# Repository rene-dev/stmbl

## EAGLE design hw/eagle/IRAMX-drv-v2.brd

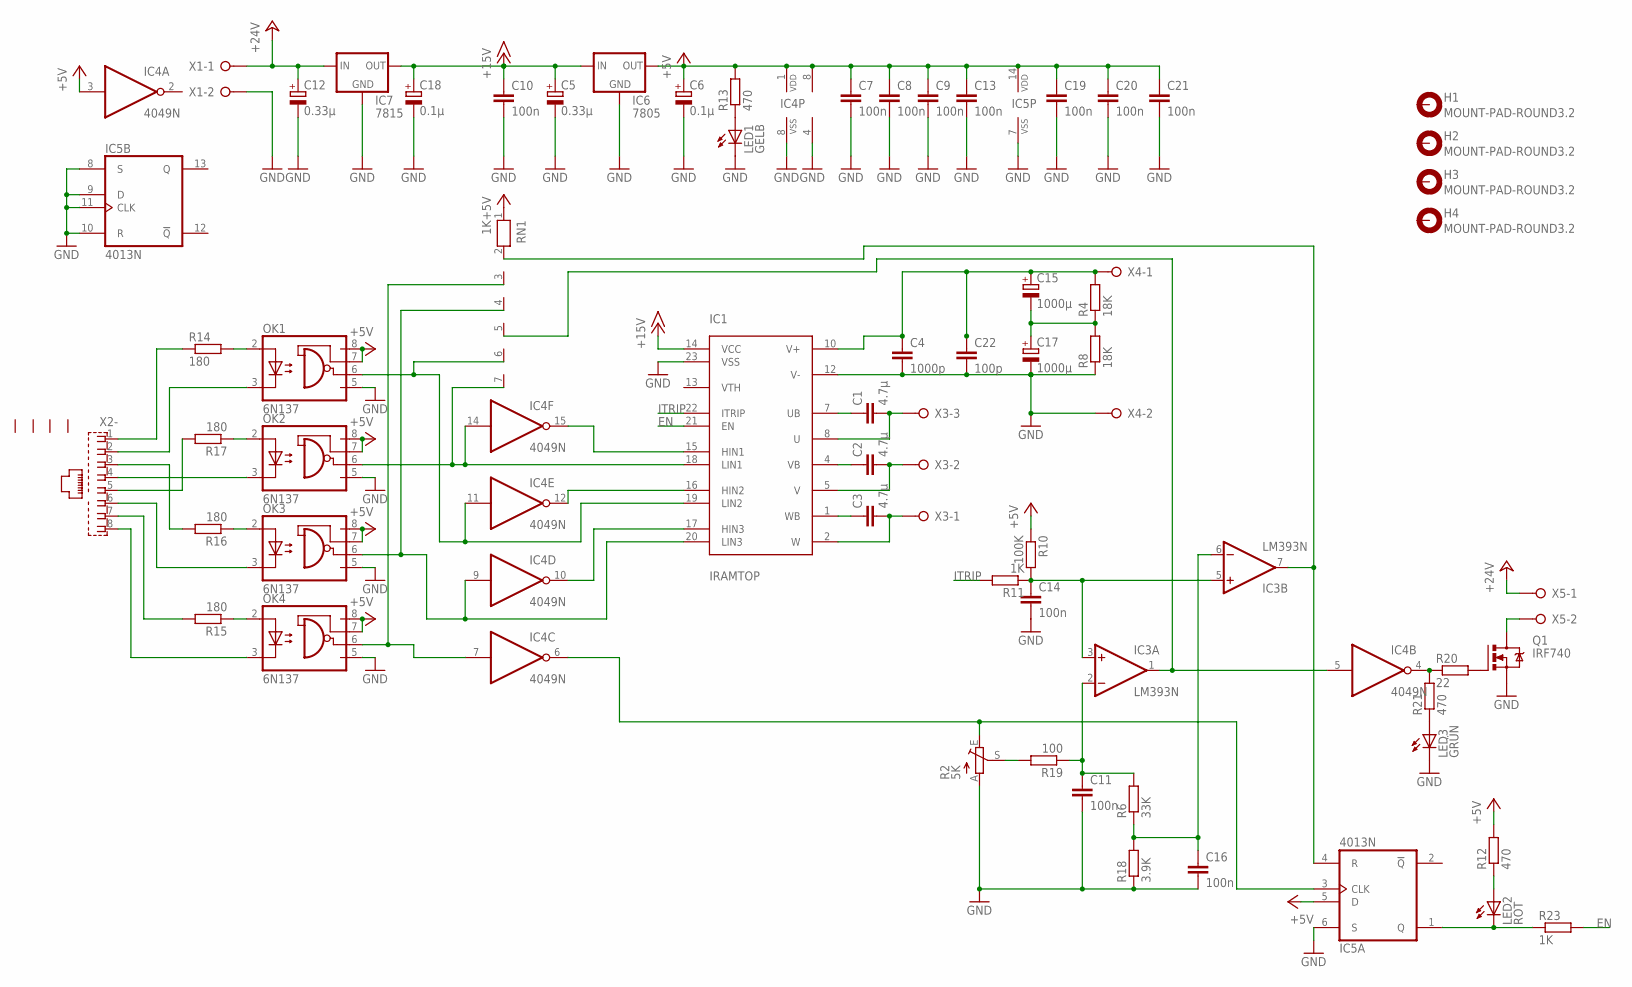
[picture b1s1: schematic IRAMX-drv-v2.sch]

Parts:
C1, C2, C3: 4.7µ; C5B7.2
C4: 1000p; C5B5
C5, C12: 0.33µ; E2,5-5
C6, C18: 0.1µ; E2,5-5
C7, C8, C9, C10, C11, C13, C14, C16, C19, C20, C21: 100n; C050-025X075
C15, C17: 1000µ; EB25D
C22: 100p; C150-054X183
H1, H2, H3, H4: MOUNT-PAD-ROUND3.2; 3,2-PAD
IC1: IRAMTOP; SIP23_TOP
IC3: LM393N; DIL08
IC4: 4049N; DIL16
IC5: 4013N; DIL14
IC6: 7805; 78XXS
IC7: 7815; 78XXS
LED1: GELB; LED5MM
LED2: ROT; LED5MM
LED3: GRÜN; LED5MM
OK1, OK2, OK3, OK4: 6N137; DIL08
Q1: IRF740; TO220BV
R2: 5K; CA6V
R4, R8: 18K; CER
R6: 33K; 0204/7
R10: 100K; 0204/7
R11, R23: 1K; 0204/7
R12, R13, R21: 470; 0204/7
R14, R15, R16, R17: 180; 0204V
R18: 3.9K; 0204/7
R19: 100; 0204/7
R20: 22; 0204/7
RN1: 1K; RN-7
X1, X4, X5: W237-02P; W237-132
X2: RJ45
X3: W237-03P; W237-133

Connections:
+5V: C6.+, C7.1, C8.1, C9.1, C13.1, C19.1, C20.1, C21.1, IC3.8 (V+), IC4.1 (VDD), IC4.3 (I), IC5.5 (D), IC5.14 (VDD), IC6.OUT, OK1.7 (VE), OK1.8 (VCC), OK2.7 (VE), OK2.8 (VCC), OK3.7 (VE), OK3.8 (VCC), OK4.7 (VE), OK4.8 (VCC), R10.1, R12.2, R13.2, RN1.1
+15V: C5.+, C10.1, C18.+, IC1.14 (VCC), IC6.IN, IC7.OUT
+24V: C12.+, IC7.IN, X1.1, X5.1
EN: IC1.21 (EN), R23.2
GND: C4.2, C5.-, C6.-, C7.2, C8.2, C9.2, C10.2, C11.2, C12.-, C13.2, C14.2, C16.2, C17.-, C18.-, C19.2, C20.2, C21.2, C22.2, IC1.12 (V-), IC1.23 (VSS), IC3.4 (V-), IC4.8 (VSS), IC5.6 (S), IC5.7 (VSS), IC5.8 (S), IC5.9 (D), IC5.10 (R), IC5.11 (CLK), IC6.GND, IC7.GND, LED1.K (C), LED3.K (C), OK1.5 (GND), OK2.5 (GND), OK3.5 (GND), OK4.5 (GND), Q1.S, R2.A, R8.P$1 (1), R18.1, X1.2, X4.2
ITRIP: IC1.22 (ITRIP), R11.2
unnamed: C1.1, IC1.7 (UB)
unnamed: C1.2, IC1.8 (U), X3.3
unnamed: C2.1, IC1.4 (VB)
unnamed: C2.2, IC1.5 (V), X3.2
unnamed: C3.1, IC1.1 (WB)
unnamed: C3.2, IC1.2 (W), X3.1
unnamed: LED2.A, R12.1
unnamed: C14.1, IC3.3 (+IN), IC3.5 (+IN), R10.2, R11.1
unnamed: LED3.A, R21.1
unnamed: IC3.1 (OUT), IC4.5 (I), RN1.5
unnamed: C15.-, C17.+, R4.P$1 (1), R8.P$2 (2)
unnamed: IC1.15 (HIN1), IC4.15 (O)
unnamed: IC1.16 (HIN2), IC4.12 (O)
unnamed: IC4.6 (O), IC5.3 (CLK), R2.E
unnamed: IC1.17 (HIN3), IC4.10 (O)
unnamed: OK3.3 (C), X2.6
unnamed: R16.2, X2.3
unnamed: OK4.3 (C), X2.8
unnamed: OK2.3 (C), X2.4
unnamed: OK1.3 (C), X2.2
unnamed: OK1.2 (A), R14.2
unnamed: R17.2, X2.5
unnamed: R15.2, X2.7
unnamed: IC1.18 (LIN1), IC4.14 (I), OK2.6 (VO), RN1.7
unnamed: R2.S, R19.2
unnamed: Q1.D, X5.2
unnamed: C11.1, IC3.2 (-IN), R6.2, R19.1
unnamed: IC5.1 (Q), LED2.K (C), R23.1
unnamed: IC4.7 (I), OK4.6 (VO), RN1.3
unnamed: R14.1, X2.1
unnamed: OK4.2 (A), R15.1
unnamed: OK3.2 (A), R16.1
unnamed: OK2.2 (A), R17.1
unnamed: IC1.19 (LIN2), IC4.11 (I), OK1.6 (VO), RN1.6
unnamed: C16.1, IC3.6 (-IN), R6.1, R18.2
unnamed: C4.1, C15.+, C22.1, IC1.10 (V+), R4.P$2 (2), X4.1
unnamed: IC1.20 (LIN3), IC4.9 (I), OK3.6 (VO), RN1.4
unnamed: IC4.4 (O), R20.1, R21.2
unnamed: Q1.G, R20.2
unnamed: IC3.7 (OUT), IC5.4 (R), RN1.2
unnamed: LED1.A, R13.1

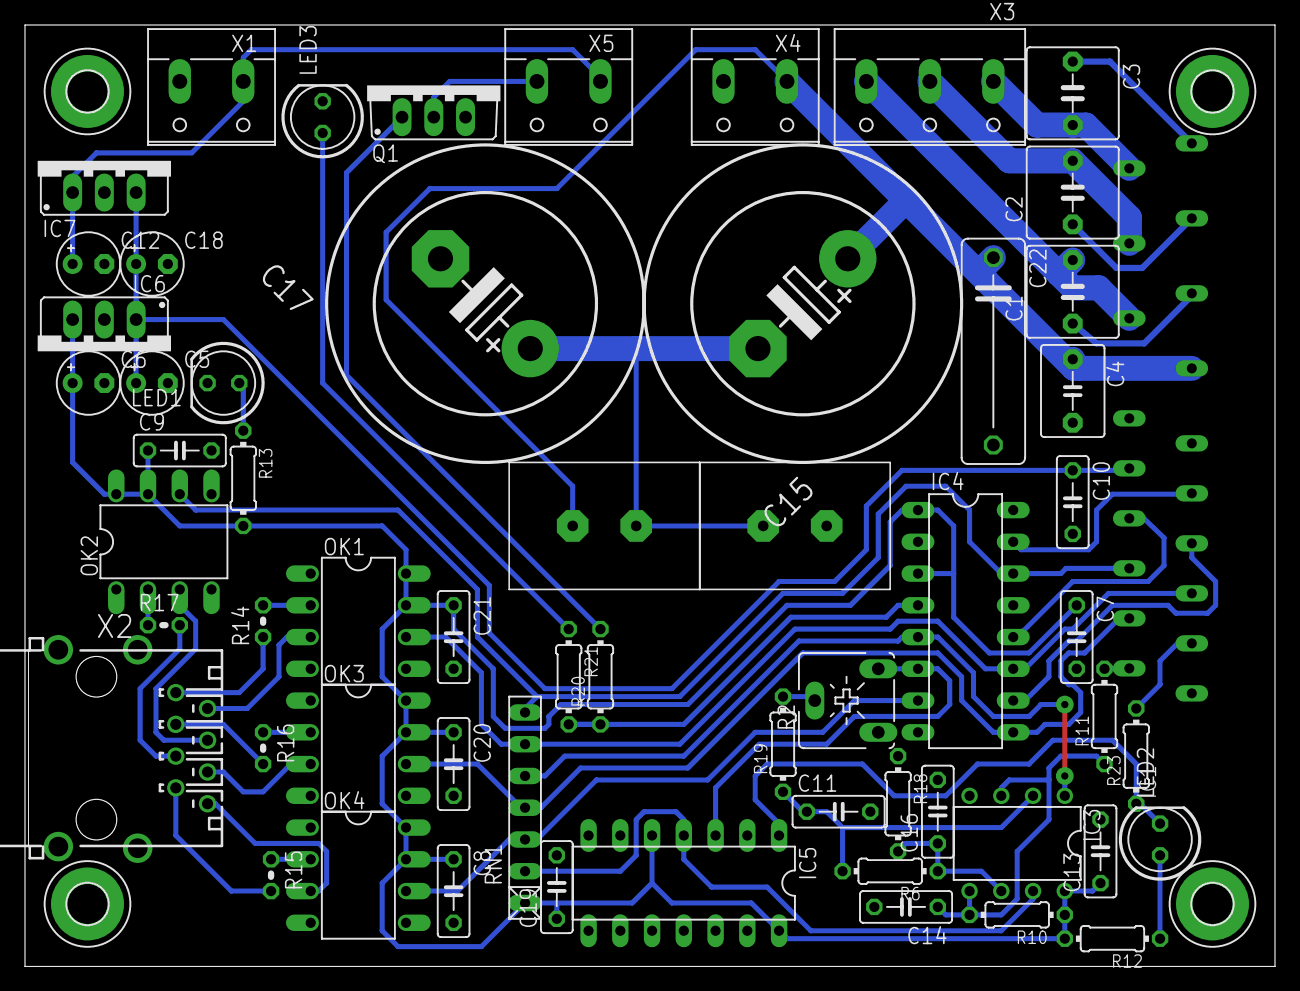
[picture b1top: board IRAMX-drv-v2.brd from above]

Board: 2 copper layers, 100.0 x 75.3 mm, 63 parts (0 on the bottom side), 47 nets.

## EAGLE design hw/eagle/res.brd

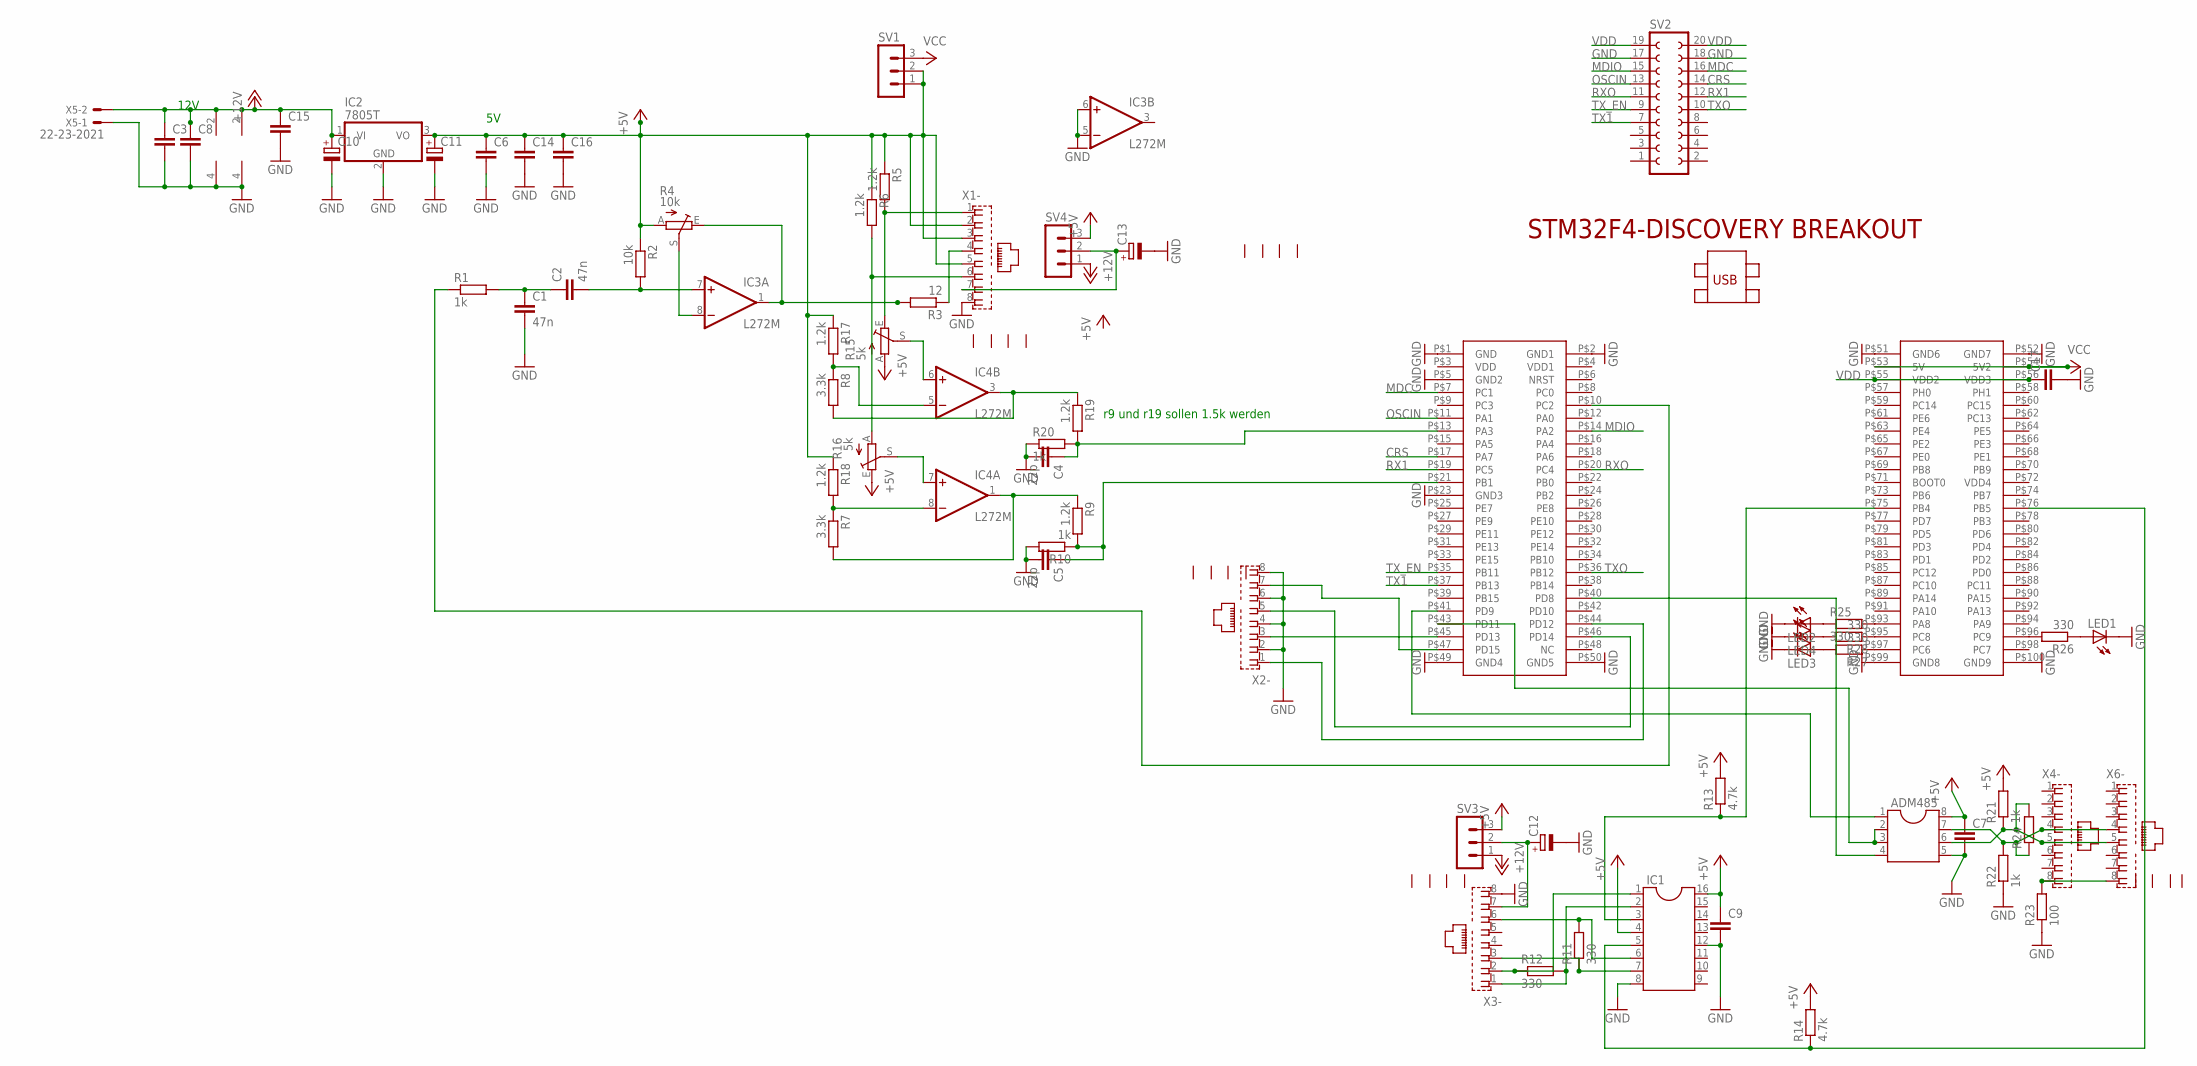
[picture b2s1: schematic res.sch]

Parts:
ADM485: DIL8; DIL08
C1, C2: 47n; C050-025X075
C3, C6, C7, C8, C9, C14, C15, C16, C17: C-EU050-025X075; C050-025X075
C4, C5: 22p; C050-025X075
C10, C11, C12, C13: CPOL-EUE2.5-5; E2,5-5
IC1: DIL16
IC2: 7805T; TO220H
IC3, IC4: L272M; DIL08
LED1, LED2, LED3, LED4: LED3MM
R1, R10, R20, R21, R22: 1k; 0204/7
R2: 10k; 0204/7
R3: 12; 0204/7
R4: 10k; CA6V
R5, R6, R9, R17, R18, R19: 1.2k; 0204/7
R7, R8: 3.3k; 0204/7
R11, R12, R25, R26, R27, R28: 330; 0204/7
R13, R14: 4.7k; 0204/7
R15, R16: 5k; CA6V
R23: 100; 0204/7
R24: R-EU_0204/7; 0204/7
SV1, SV3, SV4: MA03-1
SV2: FE10-2W
U$1: STM32F4-DISCOVERY
X1, X2, X3, X4, X6: RJ45
X5: 22-23-2021

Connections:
+5V: ADM485.8, C6.1, C7.1, C9.1, C11.+, C14.1, C16.1, IC1.4, IC1.16, IC2.3 (VO), R2.1, R4.A, R5.1, R6.1, R13.2, R14.2, R15.A, R16.E, R17.1, R18.1, R21.2, SV1.1, SV1.2, SV3.3, SV4.3, X1.2, X1.3, X1.5
+12V: C3.1, C8.1, C10.+, C15.1, IC2.1 (VI), IC3.2 (V+), IC4.2 (V+), SV3.1, SV4.1, X5.2
CRS: SV2.14, U$1.P$17 (PA7)
GND: ADM485.5, C1.2, C3.2, C4.2, C5.2, C6.2, C7.2, C8.2, C9.2, C10.-, C11.-, C12.-, C13.-, C14.2, C15.2, C16.2, C17.2, IC1.8, IC1.12, IC2.2 (GND), IC3.4 (GND), IC3.5 (-IN), IC3.6 (+IN), IC4.4 (GND), LED1.K (C), LED2.K (C), LED3.K (C), LED4.K (C), R10.2, R20.1, R22.1, R23.1, SV2.17, SV2.18, U$1.P$1 (GND), U$1.P$2 (GND1), U$1.P$5 (GND2), U$1.P$23 (GND3), U$1.P$49 (GND4), U$1.P$50 (GND5), U$1.P$51 (GND6), U$1.P$52 (GND7), U$1.P$99 (GND8), U$1.P$100 (GND9), X1.8, X2.2, X2.4, X2.6, X2.8, X3.8, X5.1
MDC: SV2.16, U$1.P$7 (PC1)
MDIO: SV2.15, U$1.P$14 (PA2)
unnamed: IC3.8 (-IN), R4.S
unnamed: IC3.1 (OUT), R3.2, R4.E
unnamed: C2.2, IC3.7 (+IN), R2.2
unnamed: R1.1, U$1.P$10 (PC2)
unnamed: C1.1, C2.1, R1.2
unnamed: R3.1, X1.4
unnamed: R6.2, R16.A, X1.6
unnamed: R5.2, R15.E, X1.1
unnamed: IC4.5 (-IN), R8.1, R17.2
unnamed: IC4.8 (-IN), R7.1, R18.2
unnamed: IC4.3 (OUT), R8.2, R19.1
unnamed: IC4.1 (OUT), R7.2, R9.1
unnamed: U$1.P$47 (PD15), X2.7
unnamed: C12.+, SV3.2, X3.7
unnamed: U$1.P$44 (PD12), X2.1
unnamed: IC1.6, R11.2, X3.6
unnamed: U$1.P$46 (PD14), X2.5
unnamed: U$1.P$45 (PD13), X2.3
unnamed: C4.1, R19.2, R20.2, U$1.P$13 (PA3)
unnamed: IC4.6 (+IN), R15.S
unnamed: IC1.3, R13.1, U$1.P$75 (PB4)
unnamed: IC1.5, R14.1, U$1.P$76 (PB5)
unnamed: IC1.2, R12.2, X3.1
unnamed: IC1.1, R12.1, X3.2
unnamed: IC1.7, R11.1, X3.3
unnamed: C13.+, SV4.2, X1.7
unnamed: IC4.7 (+IN), R16.S
unnamed: ADM485.4, U$1.P$40 (PD8)
unnamed: C5.1, R9.2, R10.1, U$1.P$21 (PB1)
unnamed: ADM485.1, U$1.P$41 (PD9)
unnamed: ADM485.2, ADM485.3, U$1.P$43 (PD11)
unnamed: ADM485.6, R21.1, R24.2, X4.5, X6.5
unnamed: ADM485.7, R22.2, R24.1, X4.4, X6.4
unnamed: R23.2, X4.8, X6.8
unnamed: LED2.A, R25.1
unnamed: R26.2, U$1.P$96 (PC9)
unnamed: R27.1, U$1.P$97 (PC6)
unnamed: R28.1, U$1.P$95 (PC8)
unnamed: LED1.A, R26.1
unnamed: R25.2, U$1.P$93 (PA8)
unnamed: LED3.A, R27.2
unnamed: LED4.A, R28.2
OSCIN: SV2.13, U$1.P$11 (PA1)
RX1: SV2.12, U$1.P$19 (PC5)
RXO: SV2.11, U$1.P$20 (PC4)
TX1: SV2.7, U$1.P$37 (PB13)
TXO: SV2.10, U$1.P$36 (PB12)
TX_EN: SV2.9, U$1.P$35 (PB11)
VCC: SV1.3, U$1.P$53 (5V), U$1.P$54 (5V2)
VDD: C17.1, SV2.19, SV2.20, U$1.P$55 (VDD2), U$1.P$56 (VDD3)

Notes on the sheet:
12V
r9 und r19 sollen 1.5k werden

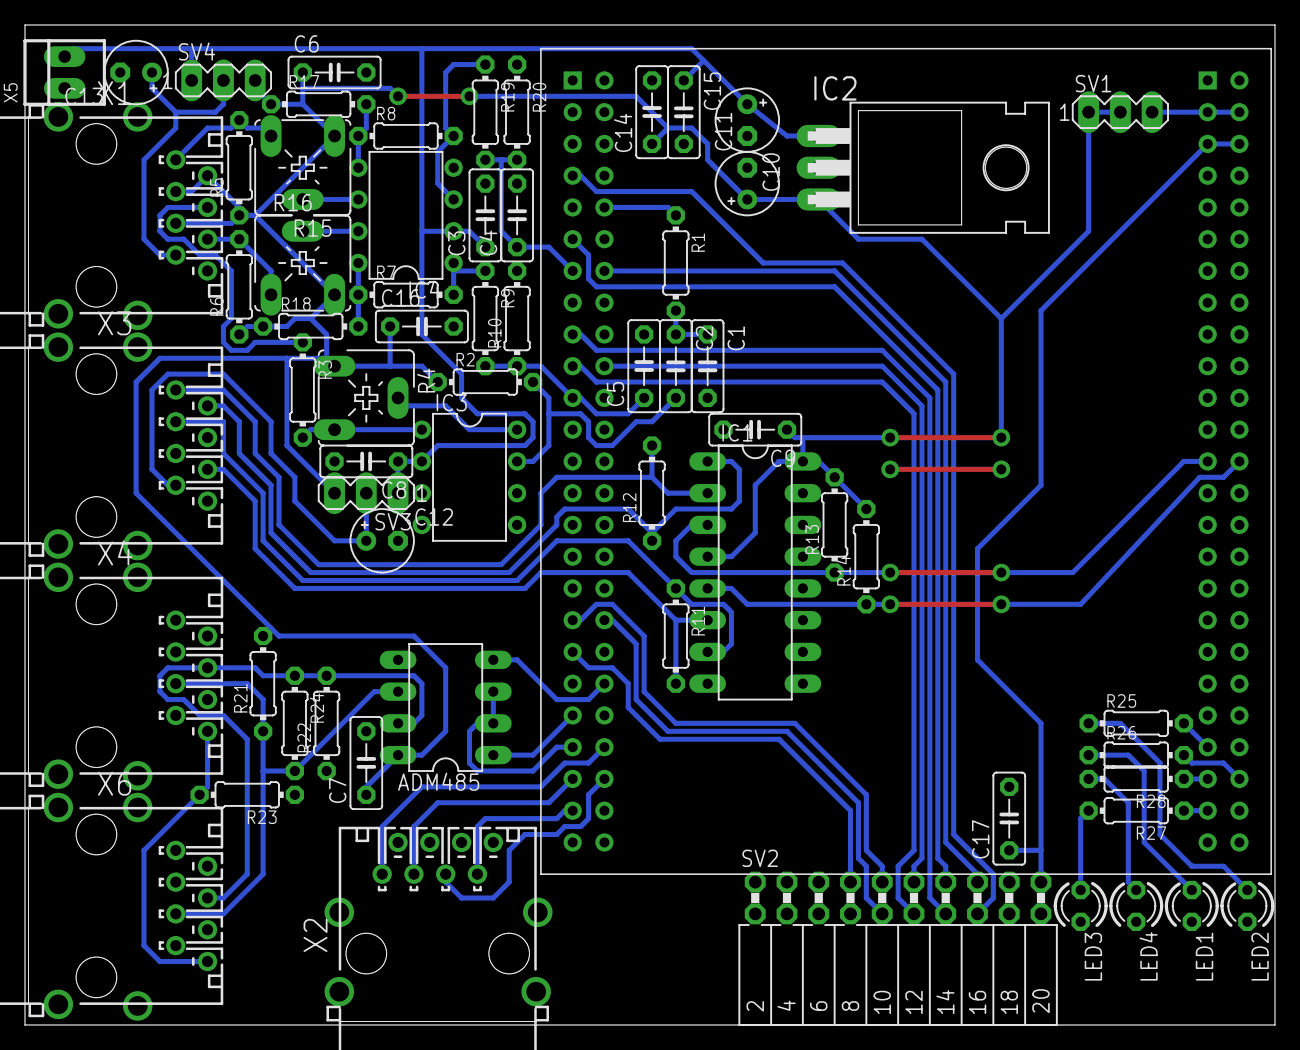
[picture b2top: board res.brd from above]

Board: 2 copper layers, 100.0 x 80.0 mm, 65 parts (0 on the bottom side), 56 nets.

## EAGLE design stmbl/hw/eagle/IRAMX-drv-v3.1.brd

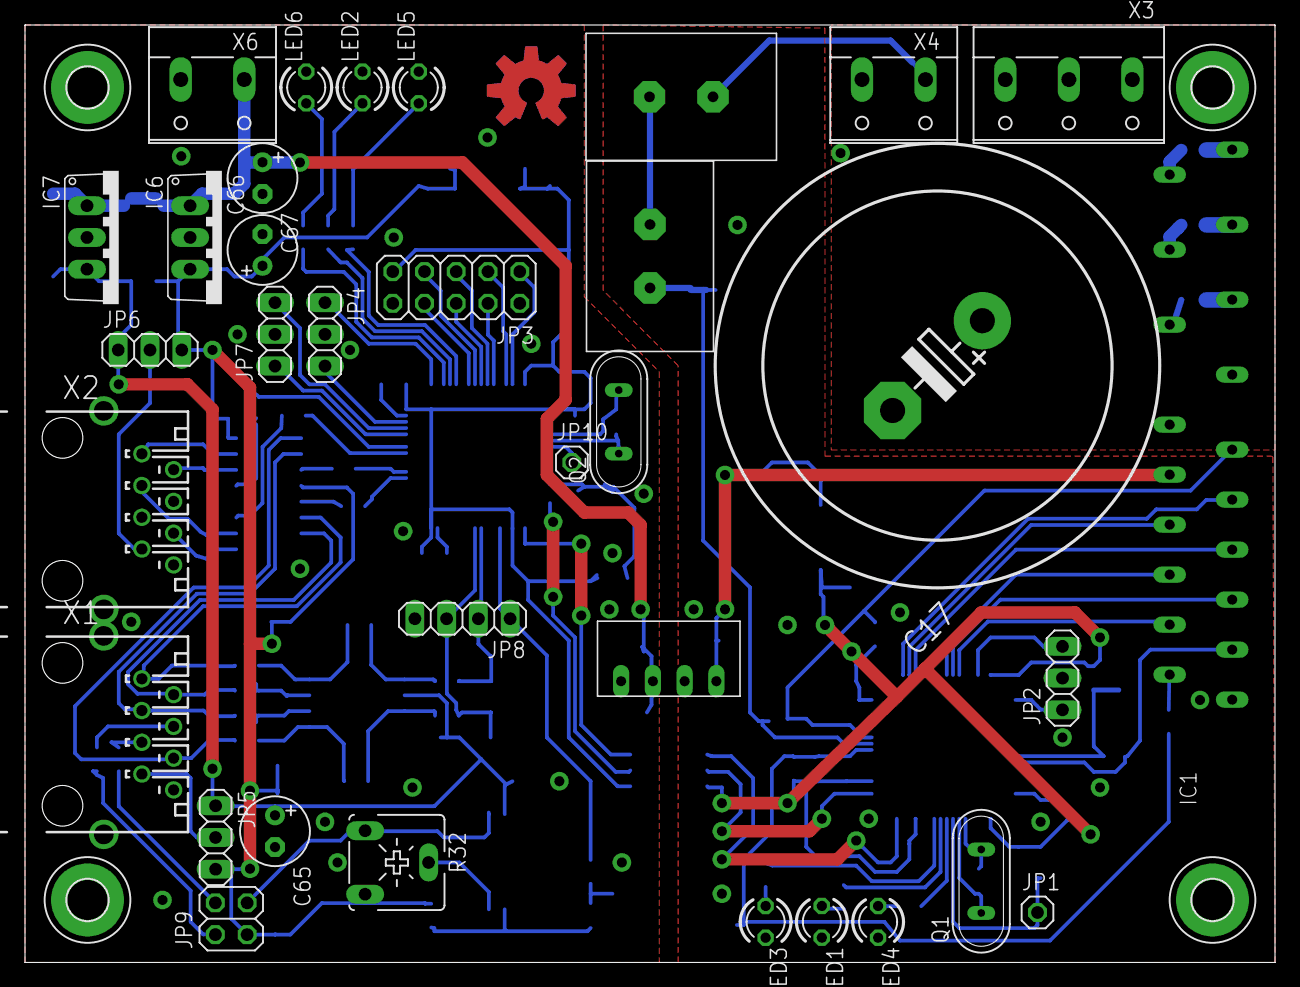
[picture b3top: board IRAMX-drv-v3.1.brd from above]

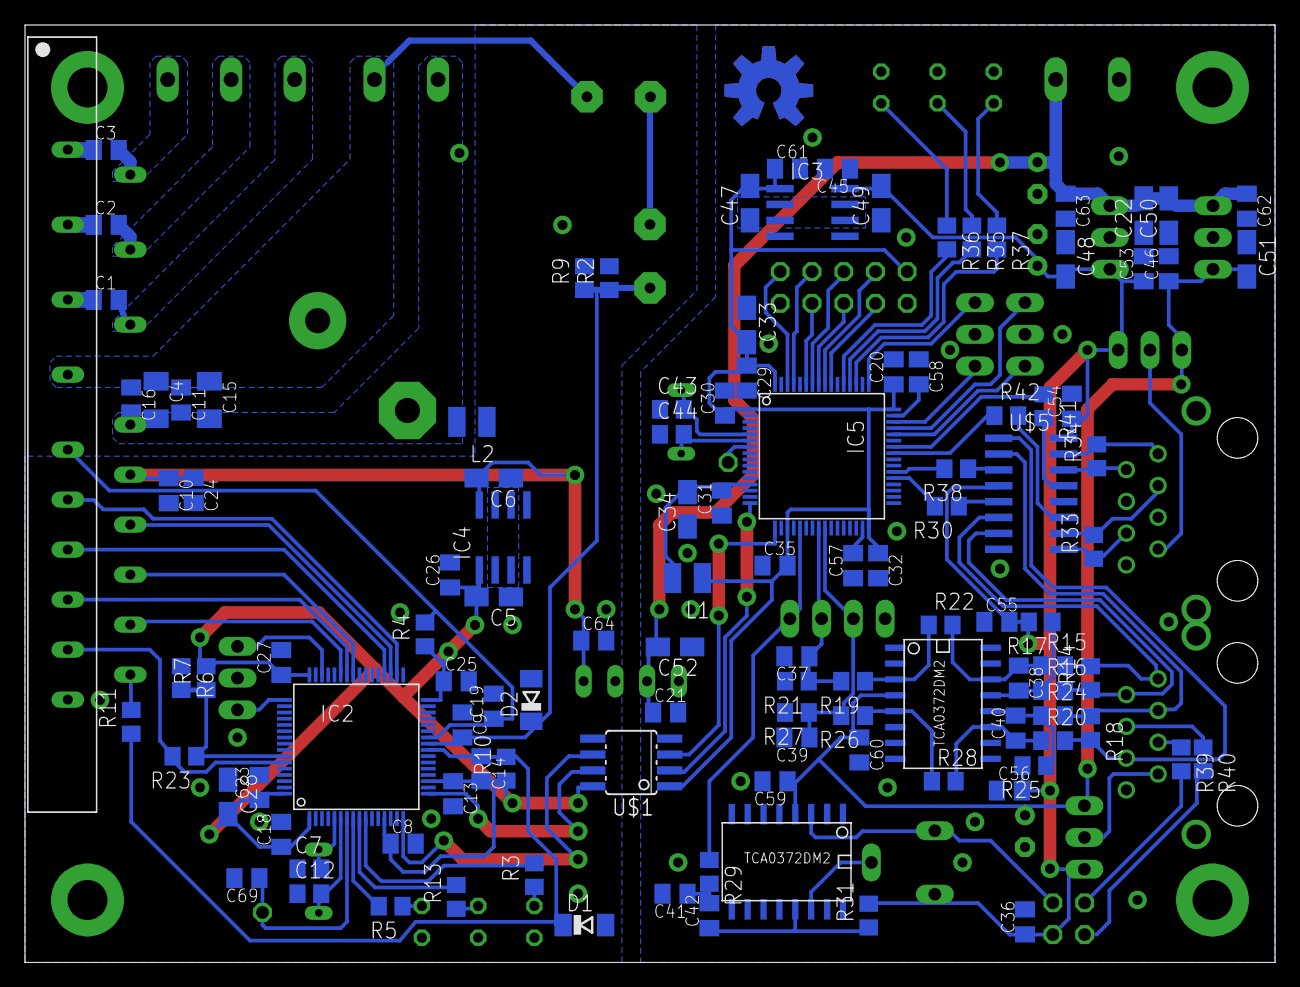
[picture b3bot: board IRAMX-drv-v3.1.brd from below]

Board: 2 copper layers, 100.0 x 75.0 mm, 154 parts (115 on the bottom side), 102 nets.

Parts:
C1, C2, C3, C24, C64: 4.7µ; C0805K
C4, C15: 100p; C1206K
C5, C28, C33, C34, C47: 10µ; A/3216-18R
C6, C22, C48, C49, C50, C51, C52: 0.33µ; A/3216-18R
C7, C12, C43, C44: 18p; C0805
C8, C9, C10, C13, C14, C18, C19, C20, C21, C23, C25, C26, C27, C29, C30, C31, C32, C35, C36, C41, C42, C45, C46, C53, C54, C55, C56, C59, C60, C61, C62, C63, C69: 100n; C0805K
C11, C16: 10n; C0805K
C17: 820µ; EB35D
C37, C38, C39, C40: 1n; C0805K
C57, C58: 2.2µ; C0805K
C65, C66, C67: 4.7µ; E2,5-6
D1, D2: 3v3; SOD80C
H1, H2, H3, H4: MOUNT-PAD-ROUND3.2; 3,2-PAD
IC1: IRAMX16UP60B; SIP23_TOP
IC2: STM32F103R6T; LQFP64
IC3, IC4: 78L05SMD; SO08
IC5: STM32F405RGT; LQFP64
IC6: 7805TV; TO220V
IC7: 7812TV; TO220V
JP1, JP10: 1X01
JP2, JP4, JP5, JP6, JP7: 1X03
JP3: 2X05
JP8: 1X04
JP9: 2X02
L1, L2: L2825P
LED1, LED2: GELB; LED3MM
LED3, LED5: GRÜN; LED3MM
LED4, LED6: ROT; LED3MM
LOGO1, LOGO2: OSHW-LOGOL; OSHW-LOGO-L
Q1, Q2: 8Mhz; QS
R1, R12: 18k; CER
R2, R9: 560; R0805
R3, R5, R13, R21, R27, R30, R35, R36, R37, R38, R41, R42: 180; R0805
R4, R10: 10k; R0805
R6, R7, R11, R15, R16, R20, R23, R24, R31, R33, R34: 1k; R0805
R14, R18, R29: 470; R0805
R17, R22, R25, R28: 3.9k; R0805
R19, R26: 330; R0805
R32: 10k; CA6V
R39, R40: 33; R0805
U$1: SI8621; SOIC08
U$2: RO-XXXX; SIP4
U$3, U$4: TCA0372DWDM2; TCA0372DM2
U$5: AM26LS32ACD; SO16
X1, X2: RJ45
X3: W237-133
X4, X6: W237-132

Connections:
+3V3_DRV: C5.+, C8.1, C13.1, C14.2, C18.1, C23.1, C25.1, C26.1, C27.1, C28.+, IC2.1, IC2.13, IC2.19, IC2.32, IC2.48, IC2.64, IC4.1, R4.1, R7.2, R10.1, U$1.8
+3V3_RES: C20.1, C29.1, C30.1, C32.1, C33.+, C35.2, C47.+, C61.1, IC3.1, IC5.1, IC5.19, IC5.32, IC5.48, IC5.64, JP3.9, L1.1, U$1.1
+5V_RES: C36.1, C45.1, C48.+, C49.+, C53.1, C54.1, C55.2, C56.2, C66.+, IC3.8, IC6.3, JP5.3, JP6.3, JP9.1, R17.2, R25.2, R31.2, R32.E, U$5.4, U$5.16
+12V_RES: C46.1, C51.+, C59.1, C60.1, C65.+, IC7.3, JP5.1, JP6.1, U$3.4, U$4.4
+15V_DRV: C6.+, C10.1, C24.1, C64.1, IC1.14, IC4.8, U$2.4
+24V_RES: C21.1, C22.+, C50.+, C52.+, C62.1, C63.1, C67.+, IC6.1, IC7.1, U$2.2, X6.1
AMP: C14.1, D1.C, IC2.24, R10.2, R11.1
CAN_RX/I2C_SCK: IC5.61, JP3.3
CAN_TX/I2C_SDA: IC5.62, JP3.1
COS: C39.1, IC5.25, JP8.3, R26.2, R27.1
E: IC2.58, R6.2, R7.1, R23.1
EN: IC1.21, IC2.59, R23.2
G: IC2.10, R3.2
GND_DRV: C5.-, C6.-, C7.1, C8.2, C9.1, C10.2, C12.1, C13.2, C18.2, C19.2, C23.2, C24.2, C25.2, C26.2, C27.2, C28.-, C64.2, C69.2, D1.A, D2.A, IC1.23, IC2.12, IC2.18, IC2.31, IC2.47, IC2.60, IC2.63, IC4.2, IC4.3, IC4.6, IC4.7, JP2.2, L2.1, LED1.K, LED3.K, LED4.K, R2.2, R6.1, R9.2, U$1.5, U$2.3
GND_RES: C20.2, C21.2, C22.-, C29.2, C30.2, C31.1, C32.2, C33.-, C34.-, C35.1, C36.2, C37.2, C39.2, C41.2, C43.1, C44.1, C45.2, C46.2, C47.-, C48.-, C49.-, C50.-, C51.-, C52.-, C53.2, C54.2, C55.1, C56.1, C57.1, C58.1, C59.2, C60.2, C61.2, C62.2, C63.2, C65.-, C66.-, C67.-, IC3.2, IC3.3, IC3.6, IC3.7, IC5.12, IC5.18, IC5.60, IC5.63, IC6.2, IC7.2, JP3.2, JP3.10, JP4.2, JP7.2, JP8.4, LED2.K, LED5.K, LED6.K, R21.2, R27.2, U$1.4, U$2.1, U$3.1, U$3.8, U$3.9, U$3.16, U$4.1, U$4.8, U$4.9, U$4.16, U$5.8, U$5.12, X1.8, X1.G3, X1.G4, X2.8, X2.G3, X2.G4, X6.2
G_RES: IC5.53, R36.2
ITRIP: IC1.22, R11.2
MISO: IC5.56, JP3.7
MOSI: IC5.57, JP3.6
unnamed: C1.1, IC1.7
unnamed: R1.P$2, R12.P$1
unnamed: C2.1, IC1.4
unnamed: LED2.A, R35.1
unnamed: C3.1, IC1.1
unnamed: R32.S, U$4.14
unnamed: LED3.A, R3.1
unnamed: LED4.A, R5.1
unnamed: C7.2, IC2.5, Q1.2
unnamed: LED5.A, R36.1
unnamed: C12.2, IC2.6, Q1.1
unnamed: C58.2, IC5.47
unnamed: C57.2, IC5.31
unnamed: C44.2, IC5.6, Q2.1
unnamed: JP5.2, X1.7
unnamed: JP9.4, R39.2
unnamed: R19.1, R22.1, U$3.3
unnamed: C38.2, R16.1, R17.1, U$3.13
unnamed: LED6.A, R37.1
unnamed: JP9.2, R40.2
unnamed: C40.2, R24.1, R25.1, U$3.12
unnamed: JP6.2, X2.7
unnamed: R26.1, R28.1, U$3.5
unnamed: R40.1, X1.4
unnamed: C40.1, R20.1, R28.2, U$3.11
unnamed: R34.2, U$5.15, X2.1
unnamed: C41.1, C42.2, R29.2
unnamed: C42.1, R31.1, U$4.13
unnamed: C38.1, R15.1, R22.2, U$3.14
unnamed: JP9.3, R32.A, U$4.3
unnamed: R39.1, X1.5
unnamed: R30.1, U$5.5
unnamed: R34.1, U$5.14, X2.2
unnamed: R33.2, U$5.10, X2.3
unnamed: R33.1, U$5.9, X2.6
unnamed: C43.2, IC5.5, Q2.2
unnamed: R18.2, R20.2, U$5.1, X1.6
unnamed: R14.1, R16.2, U$5.7, X1.2
unnamed: R42.2, U$5.11
unnamed: LED1.A, R13.1
unnamed: R41.2, U$5.13
unnamed: R38.1, U$5.3
unnamed: C31.2, C34.+, IC5.13, L1.2
unnamed: R14.2, R15.2, U$5.6, X1.1
unnamed: R18.1, R24.2, U$5.2, X1.3
NRST_RES: IC5.7, JP10.1
R: IC2.8, R5.2
RES: IC5.21, JP8.1, R29.1
RST: C69.1, IC2.7, JP1.1
RX: IC2.17, U$1.7
RX1_RES: IC5.59, JP3.4
RX2_RES: IC5.17, U$1.3
R_RES: IC5.51, R37.2
SCK: IC5.55, JP3.8
SIN: C37.1, IC5.24, JP8.2, R19.2, R21.1
SWCLK: IC2.49, JP2.1
SWCLK_RES: IC5.49, JP4.1
SWDIO: IC2.46, JP2.3
SWDIO_RES: IC5.46, JP4.3
TIM1_1: IC1.18, IC2.41
TIM1_1N: IC1.15, IC2.34
TIM1_2: IC1.19, IC2.42
TIM1_2N: IC1.16, IC2.35
TIM1_3: IC1.20, IC2.43
TIM1_3N: IC1.17, IC2.36
TIM1_A: IC5.42, R41.1
TIM1_B: IC5.41, R42.1
TIM3_A: IC5.38, R38.2
TIM3_B: IC5.37, R30.2
TX: IC2.16, U$1.6
TX1_RES: IC5.58, JP3.5
TX2_RES: IC5.16, U$1.2
U: C1.2, IC1.8, X3.3
USB_DM: IC5.44, JP7.1
USB_DP: IC5.45, JP7.3
V: C2.2, IC1.5, X3.2
V+: C4.1, C11.1, C15.1, C16.1, C17.+, IC1.10, R1.P$1, X4.1
V-: C4.2, C11.2, C15.2, C16.2, C17.-, IC1.12, L2.2, X4.2
VLT: C9.2, D2.C, IC2.25, R2.1, R9.1, R12.P$2
VTH: C19.1, IC1.13, IC2.26, R4.2
W: C3.2, IC1.2, X3.1
Y: IC2.9, R13.2
Y_RES: IC5.52, R35.2

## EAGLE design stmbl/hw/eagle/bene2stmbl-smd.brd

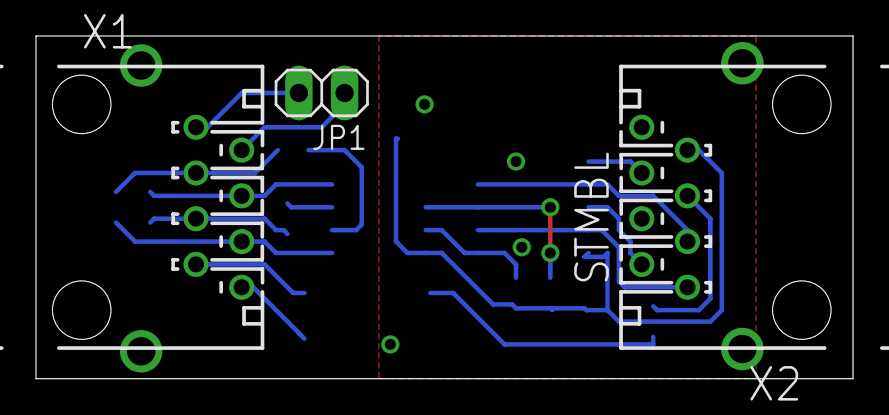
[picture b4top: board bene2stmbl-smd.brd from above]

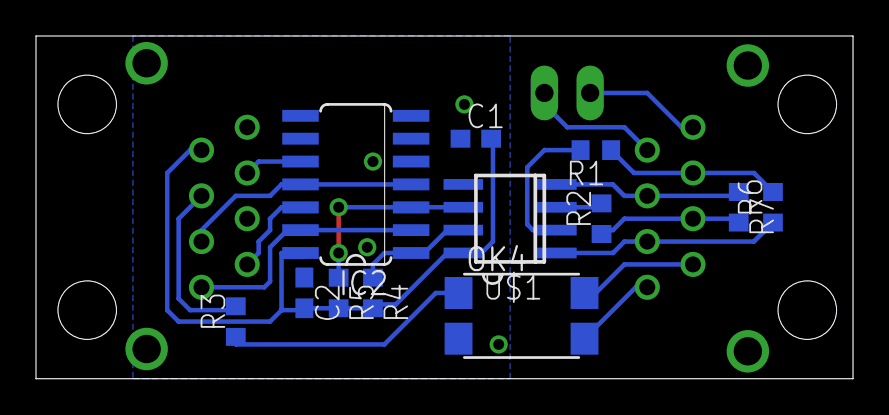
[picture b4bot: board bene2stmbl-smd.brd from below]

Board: 2 copper layers, 45.4 x 19.0 mm, 15 parts (12 on the bottom side), 20 nets.

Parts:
C1, C2: 100n; C0603
IC2: 7414D; SO14
JP1: 1X02
OK4: LTV816S; SMD4
R1, R2: 330; R0603
R3, R6, R7: R0603
R4, R5: 3k9; R0603
U$1: HCPL-053L-SMD; SO08
X1, X2: RJ45

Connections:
GND: C1.1, C2.1, IC2.5, IC2.7, IC2.9, OK4.2, U$1.5, X2.8, X2.G3, X2.G4
unnamed: OK4.3, X1.8
unnamed: OK4.4, X1.7
unnamed: IC2.2, IC2.13, X2.1
unnamed: R6.1, U$1.1, X1.6
unnamed: IC2.4, IC2.11, X2.3
unnamed: R2.1, R7.2, X1.5
unnamed: R1.2, U$1.2
unnamed: R2.2, U$1.3
unnamed: JP1.1, X1.2
unnamed: JP1.2, X1.1
unnamed: IC2.1, R4.1, U$1.7
unnamed: IC2.12, X2.2
unnamed: R1.1, R6.2, X1.3
unnamed: IC2.10, X2.6
unnamed: OK4.1, R3.1
unnamed: R7.1, U$1.4, X1.4
unnamed: R3.2, X2.5
unnamed: IC2.3, R5.1, U$1.6
VCC: C1.2, C2.2, IC2.14, R4.2, R5.2, U$1.8, X2.7

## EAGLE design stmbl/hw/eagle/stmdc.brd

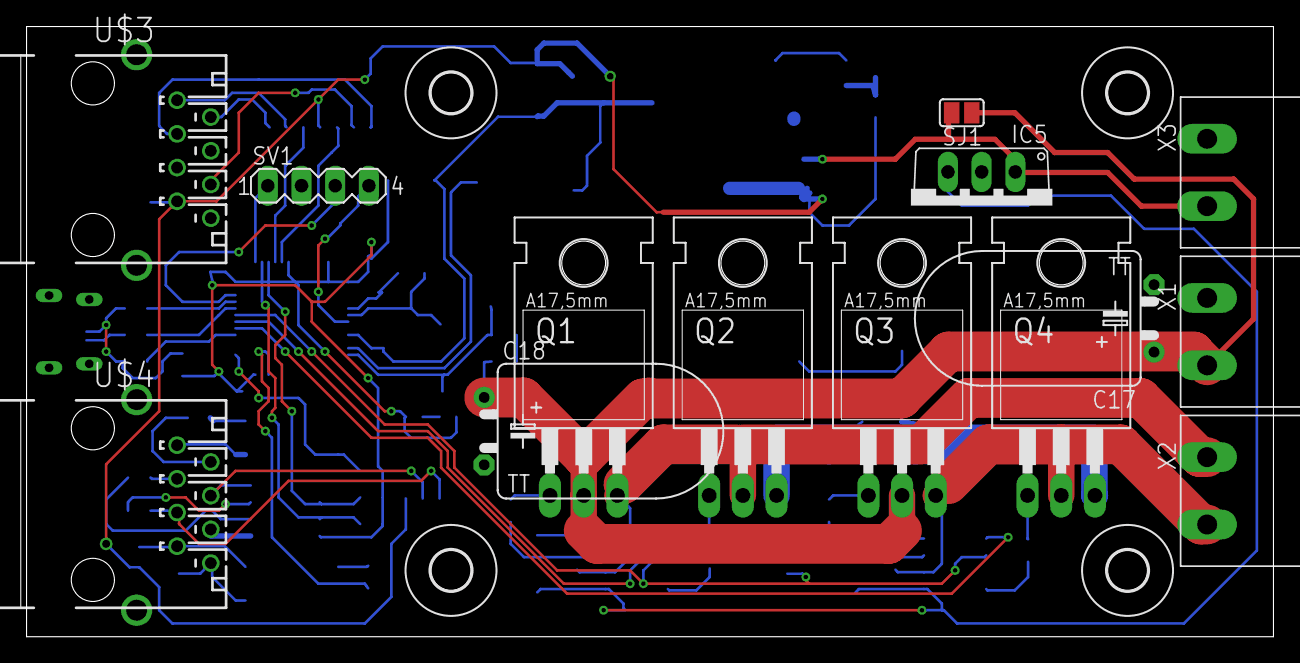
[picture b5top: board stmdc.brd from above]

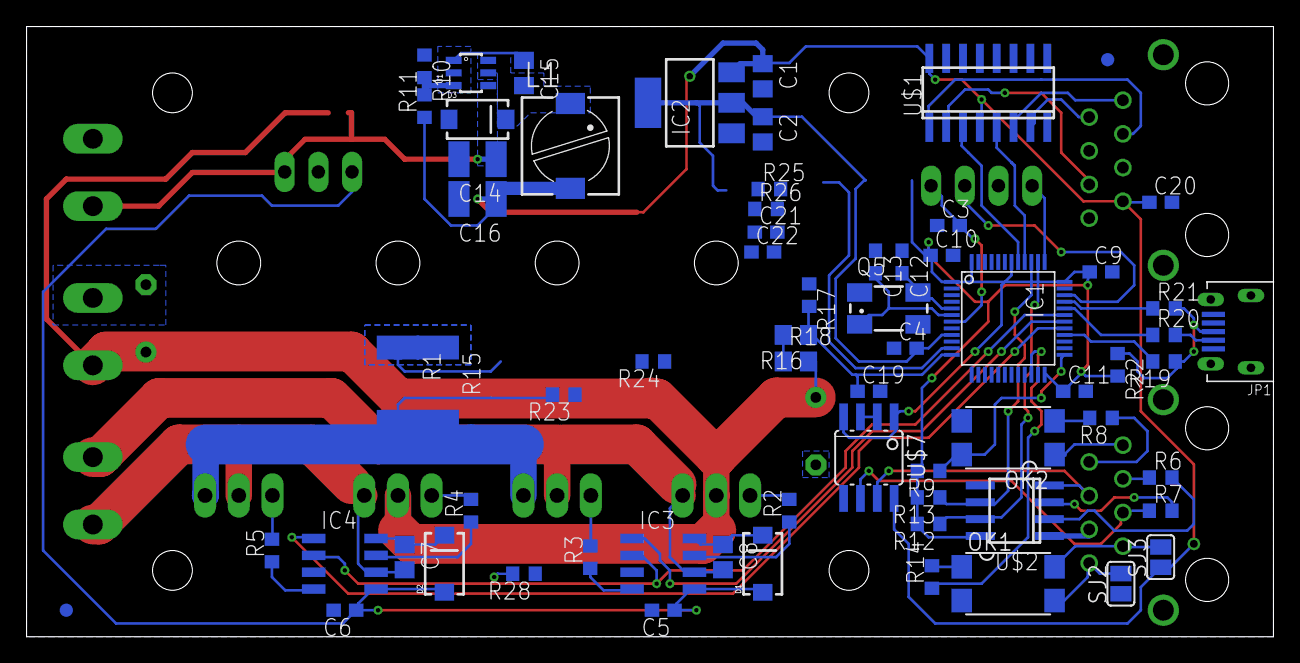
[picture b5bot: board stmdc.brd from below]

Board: 2 copper layers, 94.0 x 46.0 mm, 85 parts (67 on the bottom side), 65 nets.

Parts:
C1, C2, C7, C8, C15: C0805
C3, C4, C5, C6, C9, C10, C11, C12, C13, C19, C20: C0603
C14, C16: C1210
C17, C18: TT5D11L
C21, C22: 1n; C0603
D1, D2, D3: SMA-DIODE
H1, H2, H3, H4: MOUNT-HOLE3.0; 3,0
IC1: STM32F303CBT; LQFP48
IC2: LD117AS33TR; SOT223
IC3, IC4: IR2184S; SO08
IC5: 7815TV; TO220V
JP1: USB-RECEPTABLE; FCI-10103594-0001LF
L1: PIS2816
OK1, OK2: LTV816S; SMD4
Q1, Q2, Q3, Q4: TO220BH
Q5: CTS406
R1, R15: 0.01; R2512
R2, R3, R4, R5, R6, R7, R8, R9, R10, R11, R12, R13, R14, R17, R19, R20, R21, R22, R28: R0603
R16, R18: R0805
R23, R24: 1k; R0603
R25, R26: 15k; R0603
SJ1, SJ2, SJ3: SJ
SV1: MA04-1
U1: LMR14206; SOT23-6
U$1: AM26LS32ACD; SO16
U$2: HCPL-053L-SMD; SO08
U$3, U$4: RJ45S; RJ45
U$5, U$6: FIDUCIAL; FIDUCIAL_1MM
U$7: ADM485SOIC8; SOIC08
X1, X2, X3: AKL230-02

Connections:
3V3: C2.1, C4.2, C9.1, C10.1, C11.1, IC1.1, IC1.9, IC1.24, IC1.36, IC1.48, IC2.4, R9.2, R12.2, R13.2, R22.2, R25.2, R26.2, U$2.8
5V: C1.1, C16.1, C20.1, IC2.3, L1.2, R11.1, SJ3.1, U$1.4, U$1.16, U$3.7, U$7.8
24V: C14.1, IC5.1, SJ1.2, U1.4, U1.5, X3.2
A+: U$1.6, U$3.1
A-: U$1.7, U$3.2
B+: U$1.2, U$3.6
B-: U$1.1, U$3.3
DC_SENSE: C19.1, IC1.12, R16.1, R17.2
DIR+: U$2.4, U$4.4, U$7.7
DIR-: R7.1, U$4.5, U$7.6
EN+: OK2.1, U$4.1
EN-: R8.1, U$4.2
ERR+: OK1.4, SJ3.2, U$4.7
ERR-: OK1.3, SJ2.2, U$4.8
GND: C1.2, C2.2, C3.1, C4.1, C5.2, C6.2, C9.2, C10.2, C11.2, C12.1, C13.1, C14.2, C16.2, C17.-, C18.-, C19.2, C20.2, C21.2, C22.2, D3.A, IC1.8, IC1.23, IC1.35, IC1.44, IC1.47, IC2.1, IC3.3, IC4.3, IC5.2, JP1.5, JP1.6, JP1.7, JP1.8, JP1.9, OK1.2, OK2.3, R1.1, R10.1, R15.1, R17.1, R28.1, SJ2.1, SV1.2, U1.2, U$1.8, U$1.12, U$2.5, U$3.8, U$7.5, X1.1, X3.1
LIN: C15.2, D3.C, L1.1, U1.6
unnamed: C8.1, D1.C, IC3.8
unnamed: C8.2, IC3.6, Q1.S, Q2.D, X2.1
unnamed: C5.1, C6.1, D1.A, D2.A, IC3.5, IC4.5, IC5.3
unnamed: Q2.G, R3.2
unnamed: Q1.G, R2.2
unnamed: IC3.4, R3.1
unnamed: IC3.7, R2.1
unnamed: C7.2, IC4.6, Q3.S, Q4.D, X2.2
unnamed: C7.1, D2.C, IC4.8
unnamed: IC4.7, R4.1
unnamed: IC4.4, R5.1
unnamed: Q3.G, R4.2
unnamed: C12.2, IC1.5, Q5.3
unnamed: Q4.G, R5.2
unnamed: R16.2, R18.1
unnamed: C17.+, C18.+, Q1.D, Q3.D, R18.2, SJ1.1, X1.2
unnamed: U$7.2, U$7.3
unnamed: C13.2, IC1.6, Q5.1
unnamed: R6.2, U$2.2
unnamed: R1.P$2, R23.2
unnamed: R7.2, U$2.3
unnamed: OK2.2, R8.2
unnamed: C15.1, U1.1
unnamed: R1.P$1, R24.2
unnamed: R10.2, R11.2, U1.3
unnamed: OK1.1, R14.2
unnamed: JP1.3, R19.1, R21.2, R22.1
unnamed: JP1.2, R20.2
NRST: C3.2, IC1.7, SV1.4
S+: C22.1, IC1.17, R23.1, R25.1
S-: C21.1, IC1.18, R24.1, R26.1
SHUNT: Q2.S, Q4.S, R1.2, R15.2
STATUS: IC1.22, R14.1
STEP+: U$2.1, U$4.6
STEP-: R6.1, U$4.3
SWCLK: IC1.37, SV1.1
SWDIO: IC1.34, SV1.3
TIM1_BKIN: IC1.25, OK2.4, R9.1
TIM1_CH1: IC1.29, IC4.1
TIM1_CH2: IC1.30, IC3.1
TIM1_CH3: IC1.31, IC3.2, IC4.2, R28.2
TIM2_CH1: IC1.38, R12.1, U$2.7
TIM2_CH2: IC1.39, R13.1, U$2.6
TIM3_CH1: IC1.40, U$1.5
TIM3_CH2: IC1.41, U$1.3
USART1_TX: IC1.42, U$7.1, U$7.4
USB_DM: IC1.32, R20.1
USB_DP: IC1.33, R21.1
USB_EN: IC1.28, R19.2

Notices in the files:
parts and their libraries:
SparkFun-DiscreteSemi: Licensing: Creative Commons ShareAlike 4.0 International - https://creativecommons.org/licenses/by-sa/4.0
